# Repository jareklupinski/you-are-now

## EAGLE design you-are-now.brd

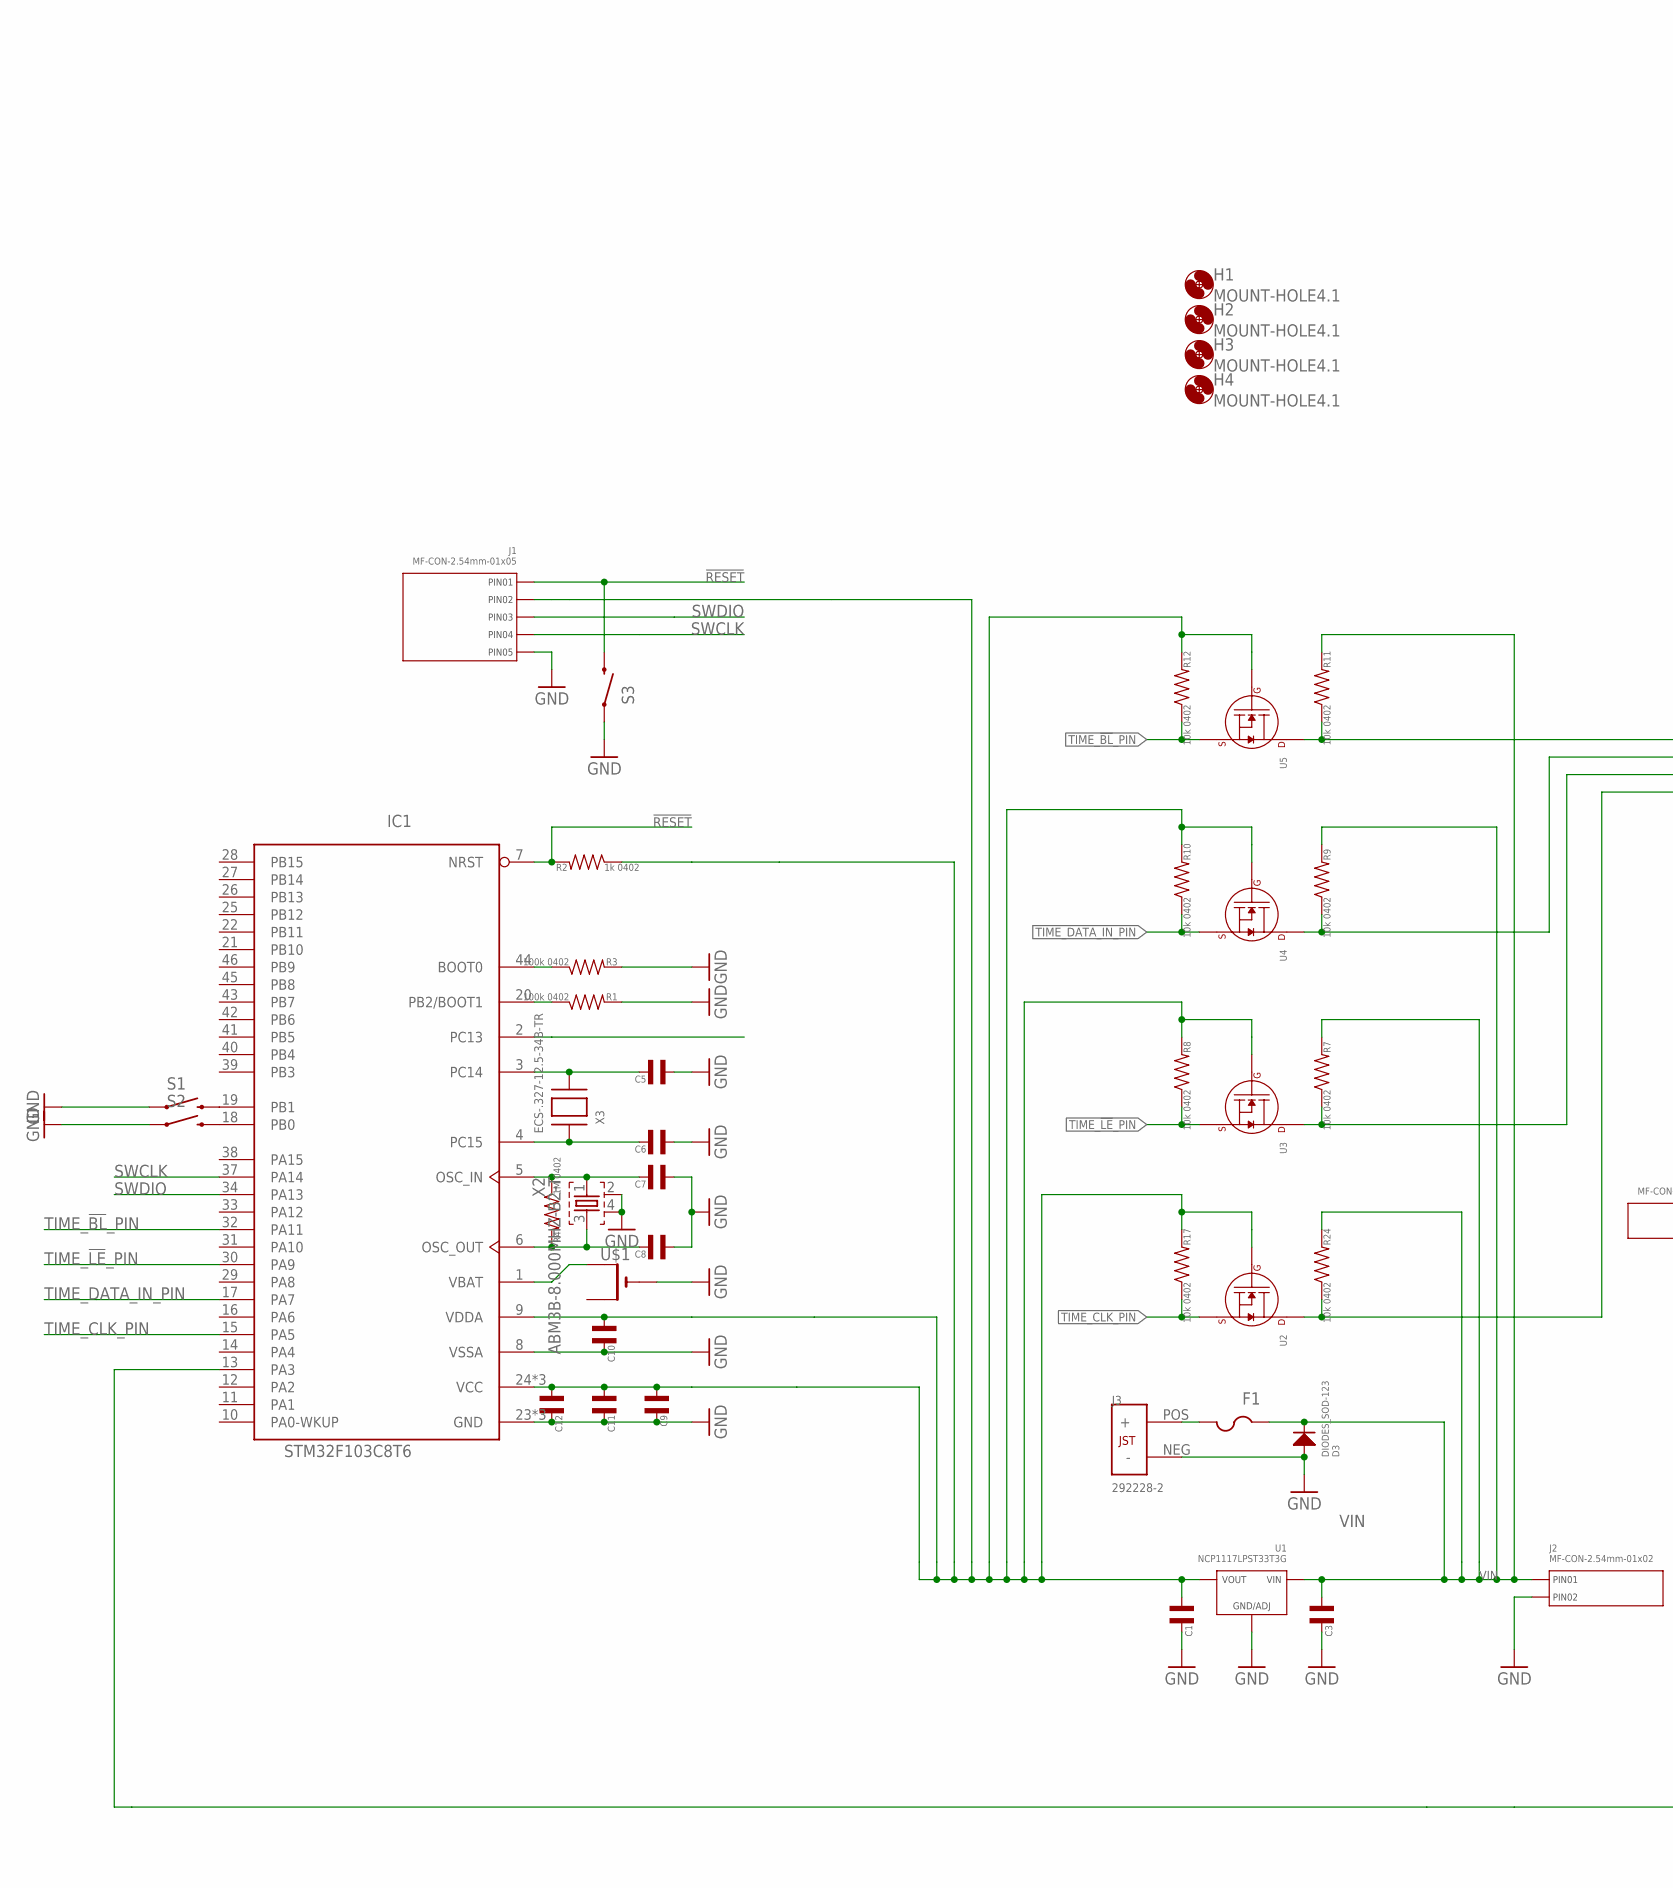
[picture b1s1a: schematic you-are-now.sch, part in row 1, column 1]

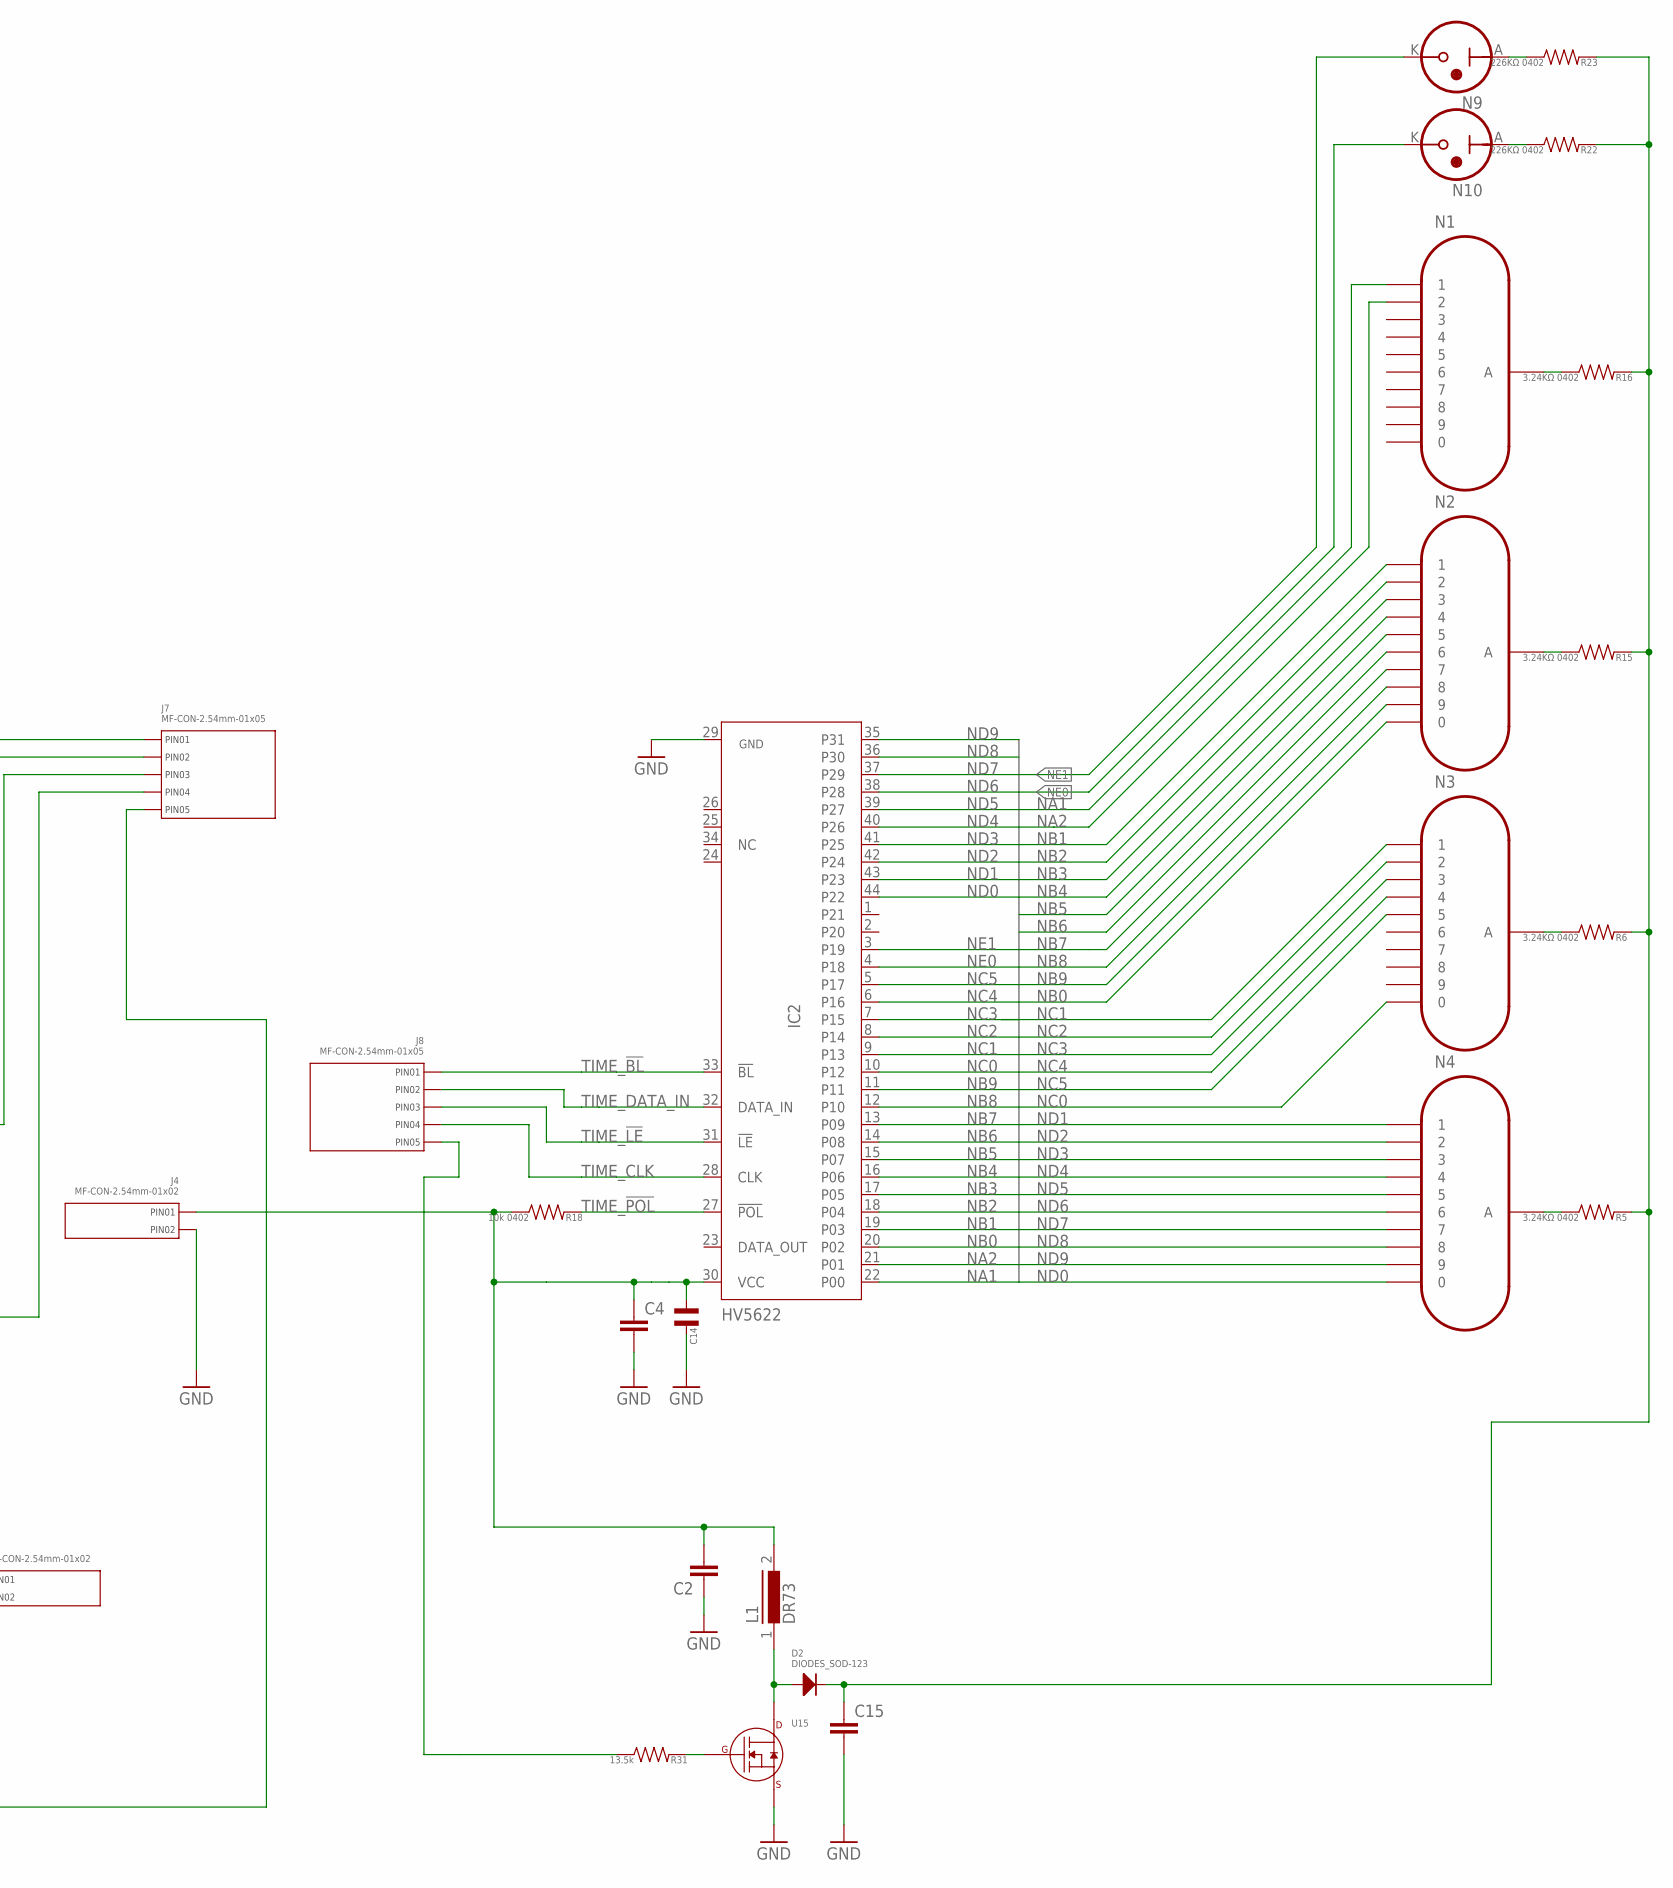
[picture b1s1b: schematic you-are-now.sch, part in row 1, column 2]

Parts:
C1, C3: CAPACITOR_NP_1206; C1206
C2, C4, C15: C-EUC1812; C1812
C5, C6, C7, C8, C9, C10, C11, C12, C14: CAPACITOR_NP_0402; C0402
D2, D3: DIODES_SOD-123; SOD-123
F1: PTCFUSE-1812; 1812
H1, H2, H3, H4: MOUNT-HOLE4.1; 4,1
IC1: STM32F103C8T6; LQFP48
IC2: HV5622; QFP44
J1, J7, J8: MF-CON-2.54mm-01x05; PTH_2.54MM_01X05
J2, J4: MF-CON-2.54mm-01x02; PTH_2.54MM_01X02
J3: 292228-2
L1: DR73
N1: Hour1; IN-12
N2: Hour2; IN-12
N3: Minutes1; IN-12
N4: Minutes2; IN-12
N9: RainyBulb; INS-1
N10: SnowyBulb; INS-1
R1, R3: 100k 0402; R0402
R2: 1k 0402; R0402
R4: 1M 0402; R0402
R5, R6, R15, R16: 3.24KΩ 0402; R0402
R7, R8, R9, R10, R11, R12, R17, R18, R24: 10k 0402; R0402
R22, R23: 226KΩ 0402; R0402
R31: 13.5k; R0402
S1, S2, S3: SWITCH-MOMENTARY-2TACTILE-SWITCH-SMD-RIGHT-ANGLE; TACTILE_SWITCH-SMD-RIGHT-ANGLE
U1: NCP1117LPST33T3G; SOT-223-3
U2, U3, U4, U5: N-CHANNEL_FET_SOT-23-3; SOT-23-3
U15: N-CHANNEL_FET_TO-252-3; TO-252-3
U$1: CR1220SMT; CR1220-SMD
X2: ABM3B-8.000MHZ-B2-T; 5.2X3.4-4-PAD
X3: ECS-.327-12.5-34B-TR; XTAL3215

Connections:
!RESET: IC1.7 (NRST), J1.P$1 (PIN1), R2.P$2, S3.2
GND: C1.P$2, C2.1, C3.P$2, C4.2, C5.P$1, C6.P$1, C7.P$1, C8.P$1, C9.P$2, C10.P$2, C11.P$2, C12.P$2, C14.P$2, C15.2, D3.ANODE, IC1.8 (VSSA), IC1.23 (GND), IC1.35 (GND), IC1.47 (GND), IC2.29 (GND), J1.P$5 (PIN5), J2.P$2 (PIN2), J3.NEG (-), J4.P$2 (PIN2), R1.P$2, R3.P$2, S1.1, S2.1, S3.1, U1.P$2 (GND/ADJ), U15.2 (SOURCE), U$1.-, X2.2, X2.4
HV9: C15.1, D2.CATHODE, R5.P$2, R6.P$2, R15.P$2, R16.P$2, R22.P$2, R23.P$2
HV_PWM: IC1.13 (PA3), J7.P$5 (PIN5)
unnamed: IC1.19 (PB1), S1.2
unnamed: N9.A, R23.P$1
unnamed: N10.A, R22.P$1
unnamed: N1.A, R16.P$1
unnamed: N2.A, R15.P$1
unnamed: N3.A, R6.P$1
unnamed: N4.A, R5.P$1
unnamed: C1.P$1, C9.P$1, C10.P$1, C11.P$1, C12.P$1, IC1.9 (VDDA), IC1.24 (VCC), IC1.36 (VCC), IC1.48 (VCC), J1.P$2 (PIN2), R2.P$1, R8.P$2, R10.P$2, R12.P$2, R17.P$2, U1.P$1 (VOUT), U1.P$3 (VOUT), U2.P$1 (GATE), U3.P$1 (GATE), U4.P$1 (GATE), U5.P$1 (GATE)
unnamed: IC1.18 (PB0), S2.2
unnamed: C2.2, C4.1, C14.P$1, IC2.30 (VCC), J4.P$1 (PIN1), L1.2, R18.P$1
unnamed: J8.P$5 (PIN5), R31.P$1
unnamed: IC1.20 (PB2/BOOT1), R1.P$1
unnamed: IC1.44 (BOOT0), R3.P$1
unnamed: C5.P$2, IC1.3 (PC14), X3.P$2
unnamed: C6.P$2, IC1.4 (PC15), X3.P$1
unnamed: C7.P$2, IC1.5 (OSC_IN), R4.P$1, X2.1
unnamed: C8.P$2, IC1.6 (OSC_OUT), R4.P$2, X2.3
unnamed: D2.ANODE, L1.1, U15.PAD (DRAIN)
unnamed: IC1.1 (VBAT), U$1.+$1 (+)
unnamed: R31.P$2, U15.1 (GATE)
unnamed: F1.2, J3.POS (+)
NA1: IC2.22 (P00), N1.1
NA2: IC2.21 (P01), N1.2
NB0: IC2.20 (P02), N2.0
NB1: IC2.19 (P03), N2.1
NB2: IC2.18 (P04), N2.2
NB3: IC2.17 (P05), N2.3
NB4: IC2.16 (P06), N2.4
NB5: IC2.15 (P07), N2.5
NB6: IC2.14 (P08), N2.6
NB7: IC2.13 (P09), N2.7
NB8: IC2.12 (P10), N2.8
NB9: IC2.11, N2.9
NC0: IC2.10 (P12), N3.0
NC1: IC2.9 (P13), N3.1
NC2: IC2.8 (P14), N3.2
NC3: IC2.7 (P15), N3.3
NC4: IC2.6 (P16), N3.4
NC5: IC2.5 (P17), N3.5
ND0: IC2.44 (P22), N4.0
ND1: IC2.43 (P23), N4.1
ND2: IC2.42 (P24), N4.2
ND3: IC2.41 (P25), N4.3
ND4: IC2.40 (P26), N4.4
ND5: IC2.39 (P27), N4.5
ND6: IC2.38 (P28), N4.6
ND7: IC2.37 (P29), N4.7
ND8: IC2.36 (P30), N4.8
ND9: IC2.35 (P31), N4.9
NE0: IC2.4 (P18), N10.K
NE1: IC2.3 (P19), N9.K
PC13: IC1.2 (PC13)
SWCLK: IC1.37 (PA14), J1.P$4 (PIN4)
SWDIO: IC1.34 (PA13), J1.P$3 (PIN3)
TIME_!BL: IC2.33 (!BL), J7.P$1 (PIN1), J8.P$1 (PIN1), R11.P$1, U5.P$3 (DRAIN)
TIME_!BL!_PIN: IC1.32 (PA11), R12.P$1, U5.P$2 (SOURCE)
TIME_!LE: IC2.31 (!LE!), J7.P$3 (PIN3), J8.P$3 (PIN3), R7.P$1, U3.P$3 (DRAIN)
TIME_!LE!_PIN: IC1.30 (PA9), R8.P$1, U3.P$2 (SOURCE)
TIME_!POL: IC2.27 (!POL!), R18.P$2
TIME_CLK: IC2.28 (CLK), J7.P$4 (PIN4), J8.P$4 (PIN4), R24.P$1, U2.P$3 (DRAIN)
TIME_CLK_PIN: IC1.15 (PA5), R17.P$1, U2.P$2 (SOURCE)
TIME_DATA_IN: IC2.32 (DATA_IN), J7.P$2 (PIN2), J8.P$2 (PIN2), R9.P$1, U4.P$3 (DRAIN)
TIME_DATA_IN_PIN: IC1.17 (PA7), R10.P$1, U4.P$2 (SOURCE)
VIN: C3.P$1, D3.CATHODE, F1.1, J2.P$1 (PIN1), R7.P$2, R9.P$2, R11.P$2, R24.P$2, U1.P$4 (VIN)

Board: 2 copper layers, 68 parts (16 on the bottom side), 67 nets, no tracks yet.

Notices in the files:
parts and their libraries:
SparkFun-Aesthetics: Licensing: CC v3.0 Share-Alike You are welcome to use this library for commercial purposes.
